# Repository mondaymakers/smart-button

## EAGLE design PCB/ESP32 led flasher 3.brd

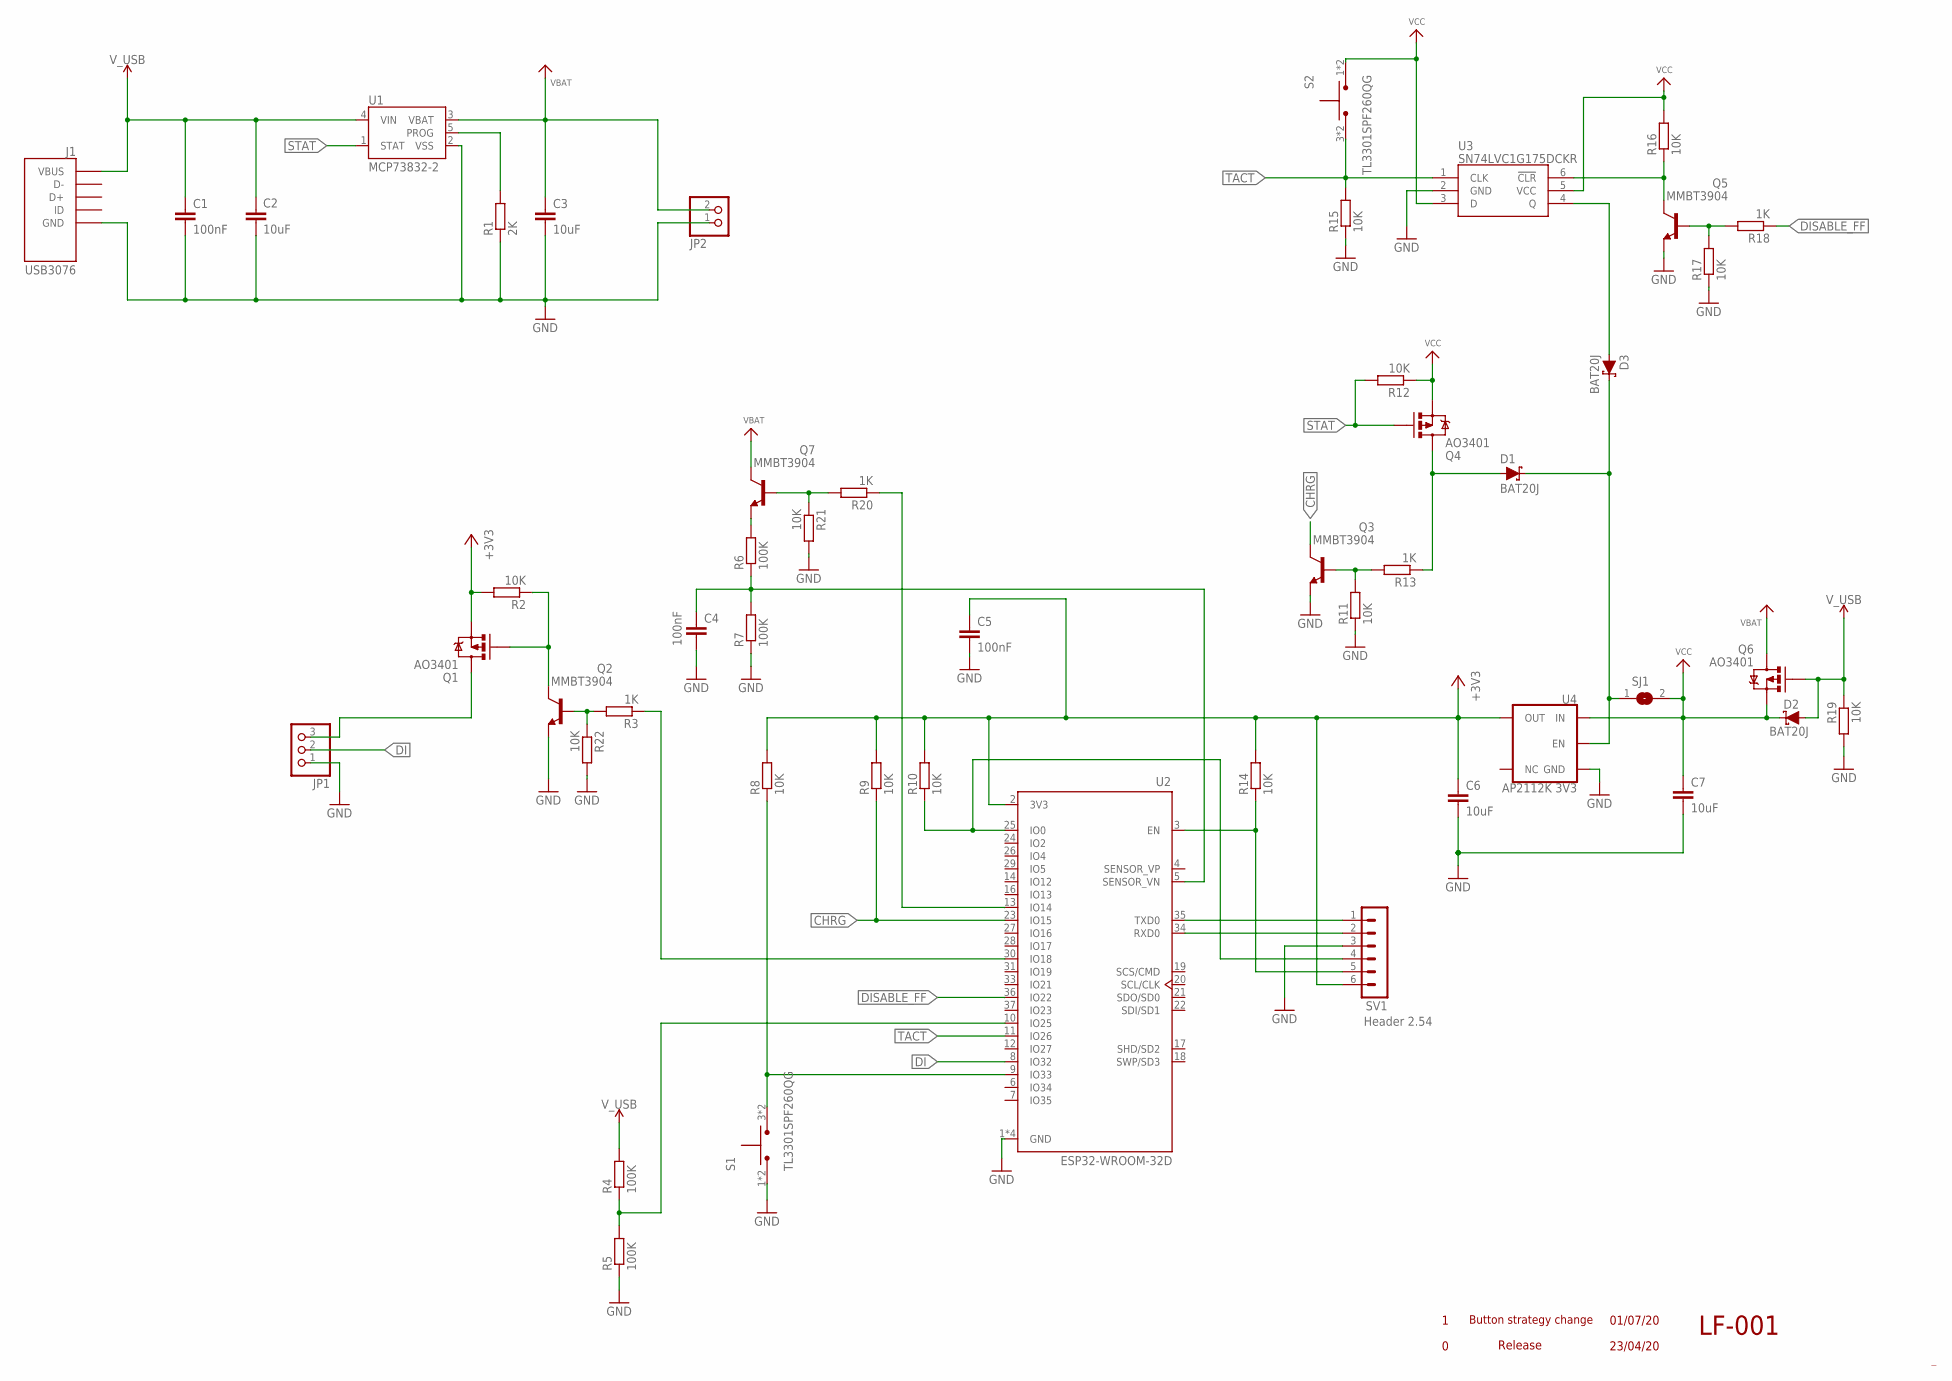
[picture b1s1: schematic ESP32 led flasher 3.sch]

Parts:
C1, C4, C5: 100nF; C0402
C2, C3, C6, C7: 10uF; C0603
D1, D2, D3: BAT20J; SOD-323
J1: USB3076; GCT_USB3076-XX-X_REVC
JP1: PINHD-1X3_2.54; 1X03
JP2: PINHD-1X2_2.54; 1X02
Q1, Q4, Q6: AO3401; SOT23-3@1
Q2, Q3, Q5, Q7: MMBT3904; SOT23
R1: 2K; R0603
R2, R8, R9, R10, R11, R12, R14, R15, R16, R17, R19, R21, R22: 10K; R0603
R3, R13, R18, R20: 1K; R0603
R4, R5, R6, R7: 100K; R0603
S1, S2: TL3301SPF260QG; SW_TL3301SPF260QG
SJ1: SOLDERJUMPERREFLOW; SOLDERJUMPER_REFLOW
SV1: Header 2.54; MA06-1
U1: MCP73832-2; SOT23-5
U2: ESP32-WROOM-32D; MODULE_ESP32-WROOM-32D
U3: SN74LVC1G175DCKR; SOP65P210X110-6N
U4: AP2112K 3V3; SOT23-5

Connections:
!CLR: Q5.3 (C), R16.1, U3.6 (!CLR)
+3V3: C5.1, C6.1, Q1.2 (S), R2.2, R8.2, R9.2, R10.2, R14.2, SV1.6, U2.2 (3V3), U4.5 (OUT)
CHRG: Q3.3 (C), R9.1, U2.23 (IO15)
DI: JP1.2, U2.8 (IO32)
DISABLE_FF: R18.1, U2.36 (IO22)
GND: C1.2, C2.2, C3.2, C4.2, C5.2, C6.2, C7.2, J1.5 (GND), JP1.1, JP2.1, Q2.2 (E), Q3.2 (E), Q5.2 (E), R1.1, R5.1, R7.1, R11.1, R15.1, R17.1, R19.2, R21.2, R22.2, S1.1, S1.2 (1), SV1.3, U1.2 (VSS), U2.1 (GND), U2.15 (GND), U2.38 (GND), U2.39 (GND), U3.2 (GND), U4.2 (GND)
unnamed: D1.A, Q4.3 (D), R13.1
unnamed: Q7.1 (B), R20.2, R21.1
unnamed: Q3.1 (B), R11.2, R13.2
unnamed: Q5.1 (B), R17.2, R18.2
unnamed: Q1.1 (G), Q2.3 (C), R2.1
unnamed: C4.1, R6.1, R7.2, U2.5 (SENSOR_VN)
unnamed: Q7.2 (E), R6.2
unnamed: R10.1, SV1.4, U2.25 (IO0)
unnamed: R14.1, SV1.5, U2.3 (EN)
unnamed: R1.2, U1.5 (PROG)
unnamed: SV1.1, U2.35 (TXD0)
unnamed: SV1.2, U2.34 (RXD0)
unnamed: R20.1, U2.13 (IO14)
unnamed: D3.A, U3.4 (Q)
unnamed: Q2.1 (B), R3.2, R22.1
unnamed: D1.C, D3.C, SJ1.1, U4.3 (EN)
unnamed: R8.1, S1.3 (2), S1.4 (2), U2.9 (IO33)
unnamed: R3.1, U2.30 (IO18)
unnamed: JP1.3, Q1.3 (D)
unnamed: R4.1, R5.2, U2.10 (IO25)
STAT: Q4.1 (G), R12.2, U1.1 (STAT)
TACT: R15.2, S2.3 (2), S2.4 (2), U2.11 (IO26), U3.1 (CLK)
VBAT: C3.1, JP2.2, Q6.3 (D), Q7.3 (C), U1.3 (VBAT)
VCC: C7.1, D2.C, Q4.2 (S), Q6.2 (S), R12.1, R16.2, S2.1, S2.2 (1), SJ1.2, U3.3 (D), U3.5 (VCC), U4.1 (IN)
V_USB: C1.1, C2.1, D2.A, J1.1 (VBUS), Q6.1 (G), R4.2, R19.1, U1.4 (VIN)

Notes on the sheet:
LF-001
Release
23/04/20
Button strategy change
01/07/20

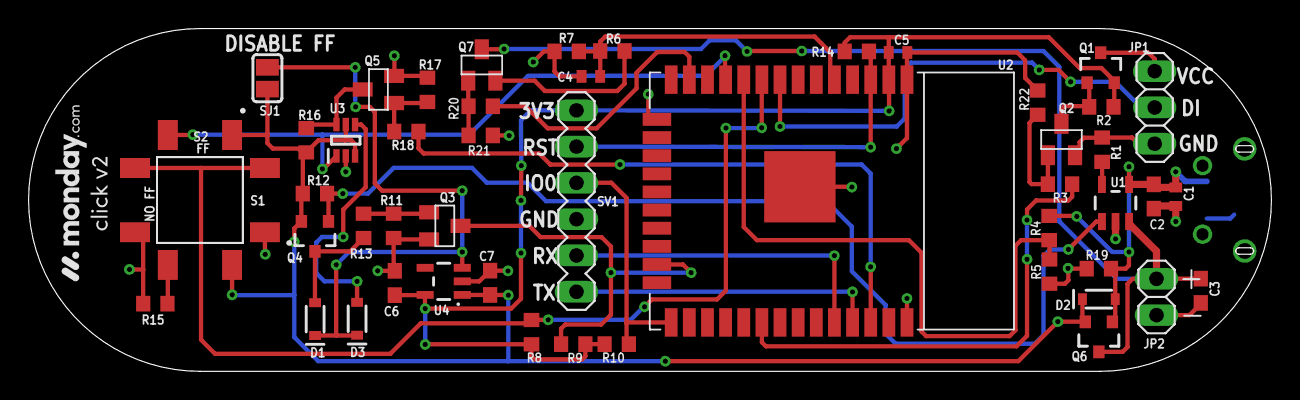
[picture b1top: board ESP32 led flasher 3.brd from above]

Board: 2 copper layers, 87.0 x 24.0 mm, 50 parts (1 on the bottom side), 31 nets.

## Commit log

2021-11-16 initial upload

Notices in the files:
parts and their libraries:
SparkFun-DiscreteSemi: Licensing: Creative Commons ShareAlike 4.0 International - https://creativecommons.org/licenses/by-sa/4.0
SparkFun-PowerIC: Licensing: CC v3.0 Share-Alike You are welcome to use this library for commercial purposes.
